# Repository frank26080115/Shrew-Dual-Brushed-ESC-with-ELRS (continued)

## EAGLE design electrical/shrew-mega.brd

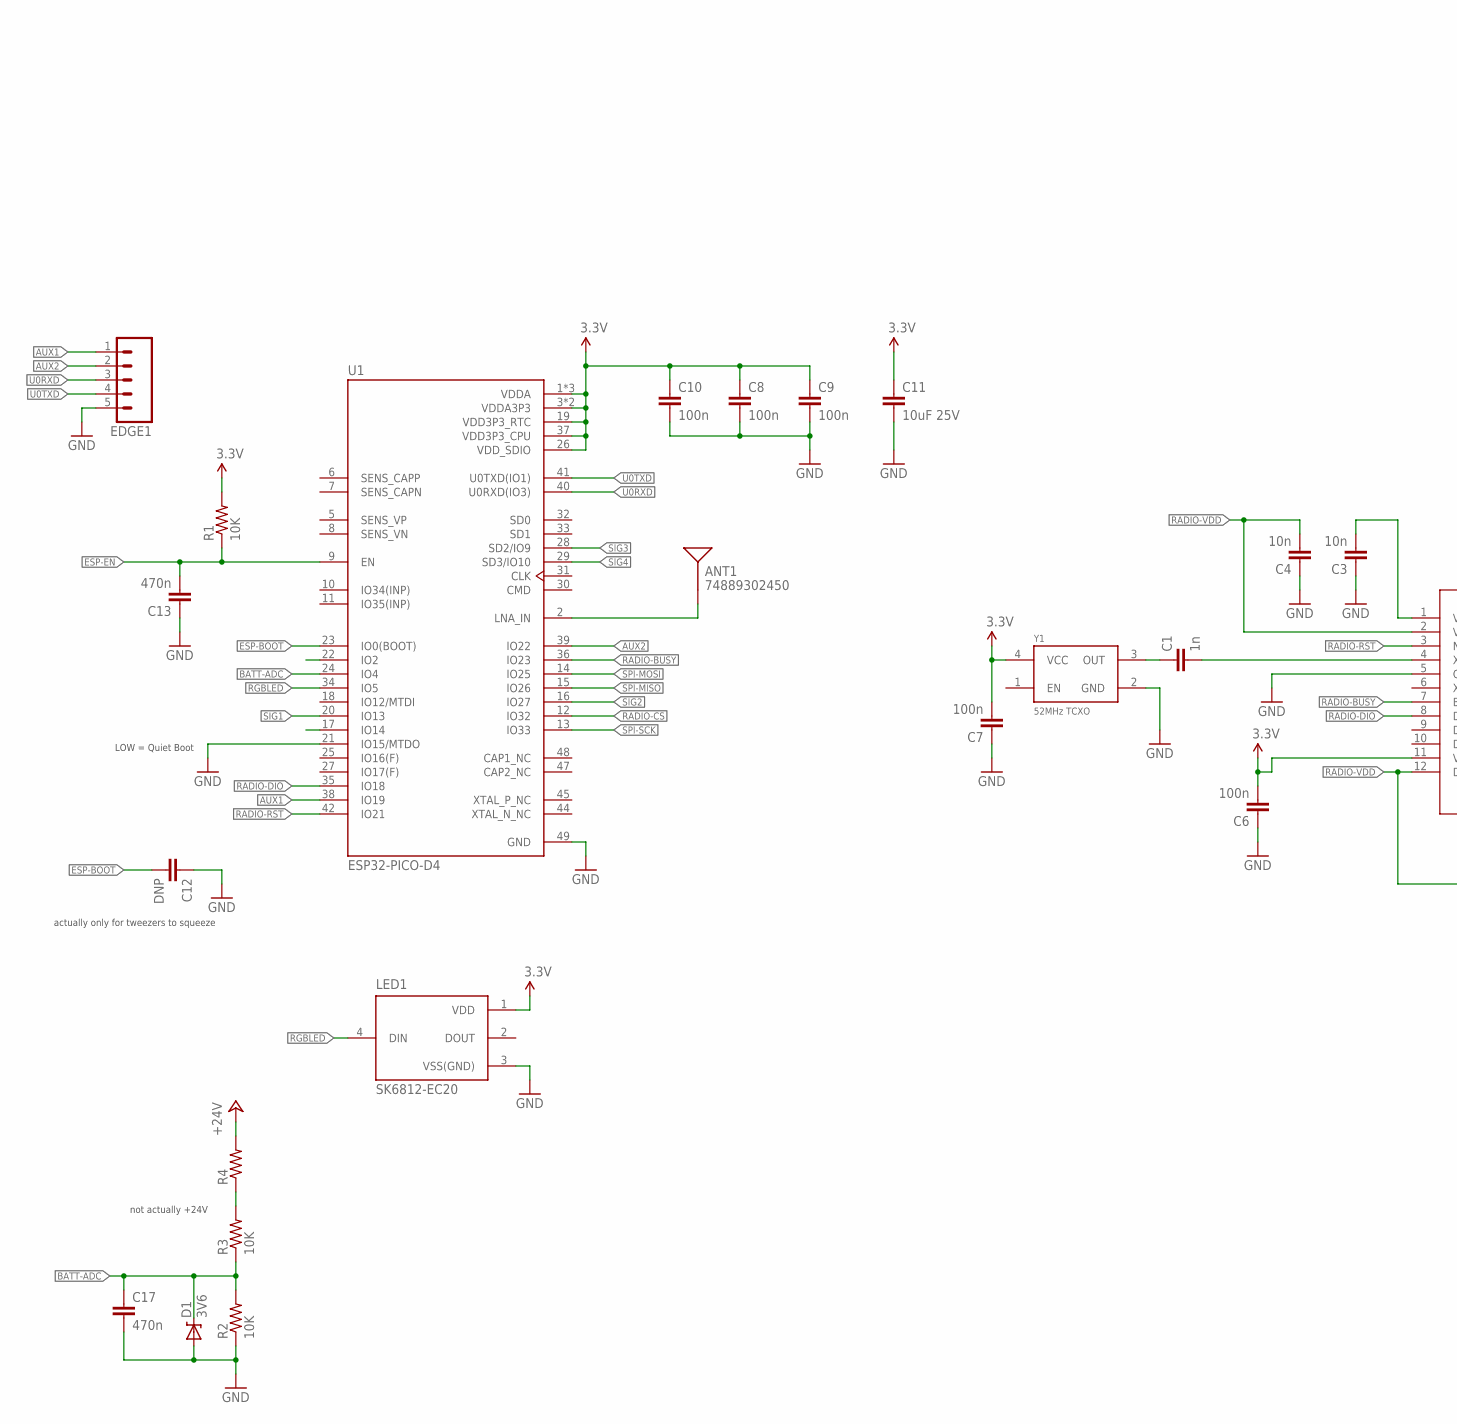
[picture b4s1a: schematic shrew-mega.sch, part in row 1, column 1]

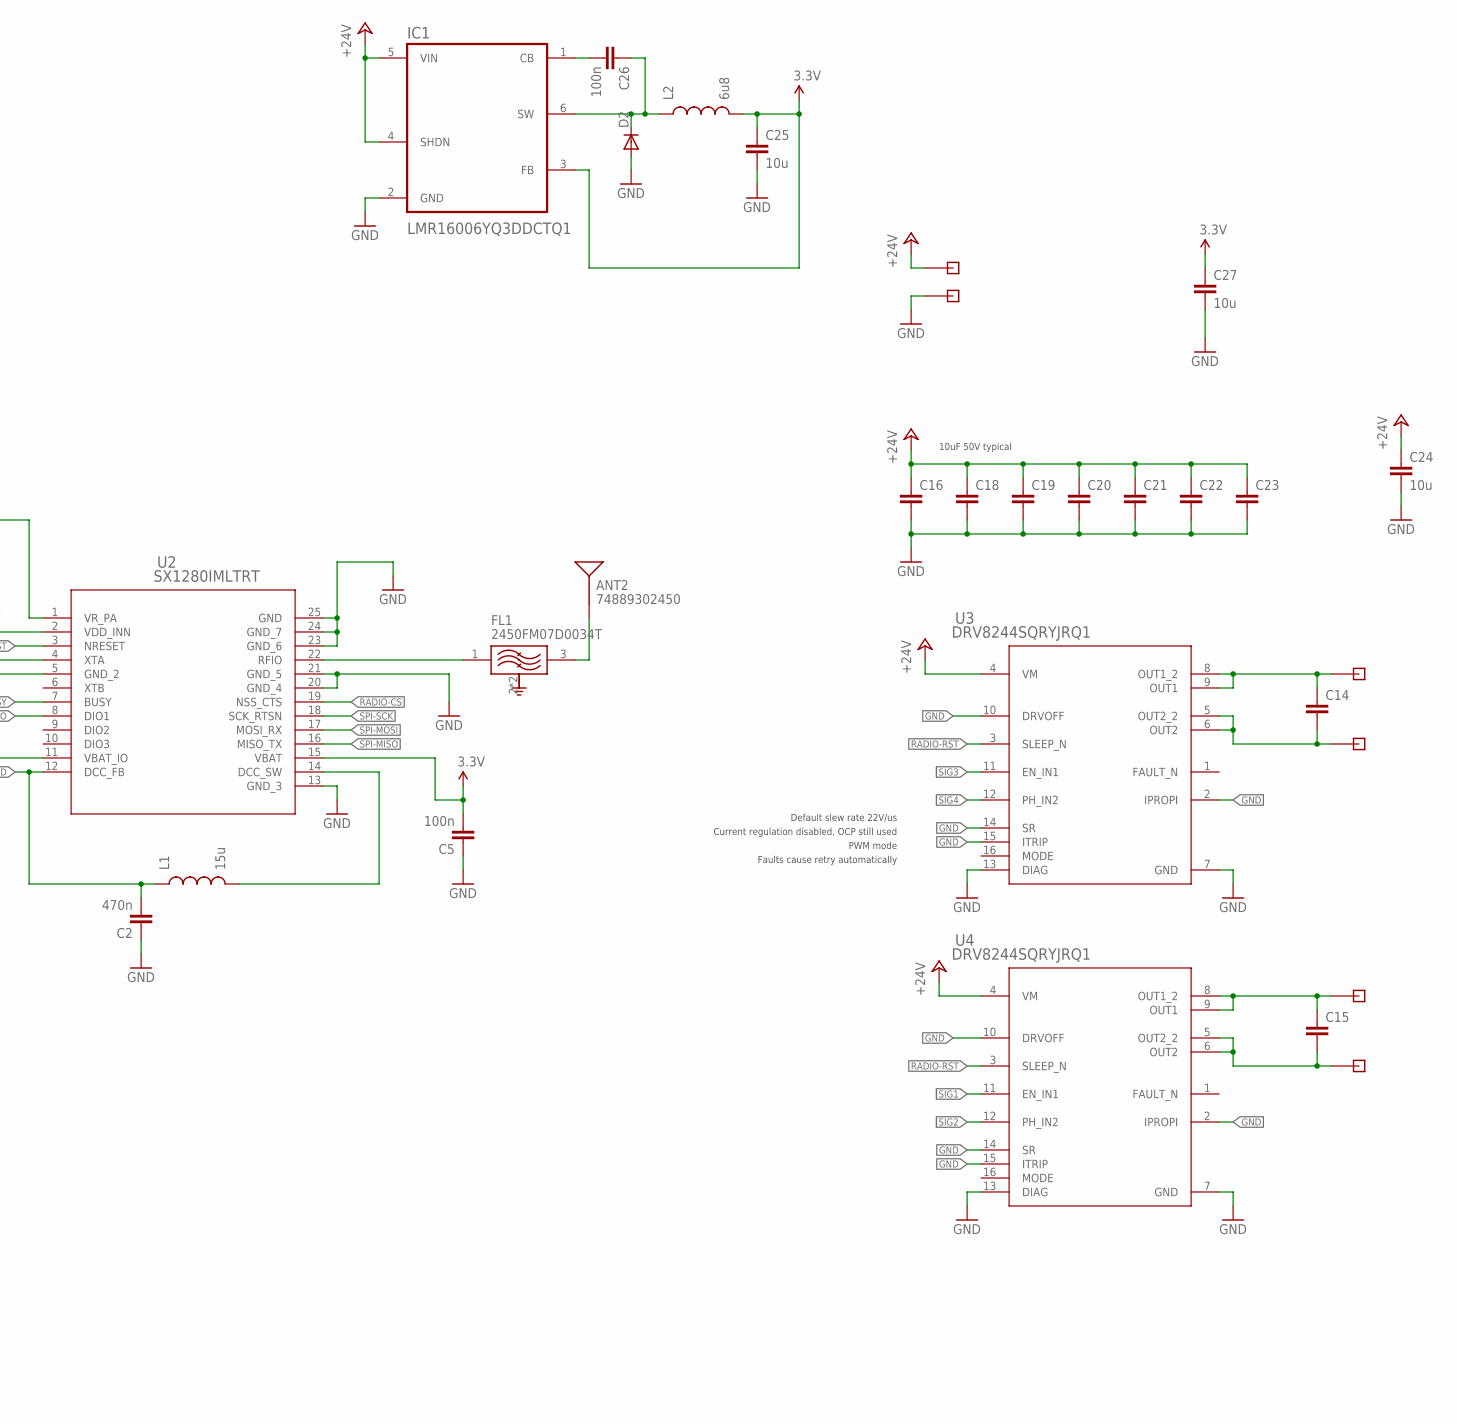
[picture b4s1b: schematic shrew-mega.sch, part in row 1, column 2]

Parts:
ANT1, ANT2: 74889302450; ANTENNA-CHIP2
C1: 1n; 0402-REV
C2, C13, C17: 470n; 0402-REV
C3, C4: 10n; 0402-REV
C5, C6, C7, C8, C9, C10, C26: 100n; 0402-REV
C11: 10uF 25V; 0805
C12: DNP; 0402-CAP
C14, C15: CAP0402-CAP; 0402-CAP
C16, C18, C19, C20, C21, C22, C23: CAP0805; 0805
C24, C25, C27: 10u; 0805
D1: 3V6; SOD-323
D2: DIODESOD; SOD-323
EDGE1: M05PTH; 1X05
FL1: 2450FM07D0034T; FIL_2450FM07D0034T
IC1: LMR16006YQ3DDCTQ1; SOT95P280X110-6N
L1: 15u; 0805
L2: 6u8; 0805
LED1: SK6812-EC20
R1, R2, R3: 10K; 0402-REV
R4: RESISTOR0402-REV; 0402-REV
U1: ESP32-PICO-D4; PQFN50P700X700X104-49N
U2: SX1280IMLTRT; QFN24_4X4_SEM
U3, U4: DRV8244SQRYJRQ1; RYJ0016A-MFG
X1, X2, X3, X4, X5, X6: PIN-1X-BIG; PAD-1X-BIG
Y1: 52MHz TCXO; OSC_TG2016SMN_50.0000M-ECGNNMB

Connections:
3.3V: C5.2, C6.2, C7.2, C8.1, C9.1, C10.1, C11.1, C25.1, C27.1, IC1.3 (FB), L2.2, LED1.1 (VDD), R1.2, U1.1 (VDDA), U1.3 (VDDA3P3), U1.4 (VDDA3P3), U1.19 (VDD3P3_RTC), U1.26 (VDD_SDIO), U1.37 (VDD3P3_CPU), U1.43 (VDDA), U1.46 (VDDA), U2.11 (VBAT_IO), U2.15 (VBAT), Y1.4 (VCC)
+24V: C16.1, C18.1, C19.1, C20.1, C21.1, C22.1, C23.1, C24.1, IC1.4 (SHDN), IC1.5 (VIN), R4.2, U3.4 (VM), U4.4 (VM), X5.1
AUX1: EDGE1.1, U1.38 (IO19)
AUX2: EDGE1.2, U1.39 (IO22)
BATT-ADC: C17.1, D1.1 (C), R2.2, R3.1, U1.24 (IO4)
ESP-BOOT: C12.2, U1.23 (IO0(BOOT))
ESP-EN: C13.2, R1.1, U1.9 (EN)
GND: C2.1, C3.1, C4.1, C5.1, C6.1, C7.1, C8.2, C9.2, C10.2, C11.2, C12.1, C13.1, C16.2, C17.2, C18.2, C19.2, C20.2, C21.2, C22.2, C23.2, C24.2, C25.2, C27.2, D1.2 (A), D2.2 (A), EDGE1.5, FL1.2 (GND), FL1.4 (GND), IC1.2 (GND), LED1.3 (VSS(GND)), R2.1, U1.21 (IO15/MTDO), U1.49 (GND), U2.5 (GND_2), U2.13 (GND_3), U2.20 (GND_4), U2.21 (GND_5), U2.23 (GND_6), U2.24 (GND_7), U2.25 (GND), U3.2 (IPROPI), U3.7 (GND), U3.10 (DRVOFF), U3.13 (DIAG), U3.14 (SR), U3.15 (ITRIP), U4.2 (IPROPI), U4.7 (GND), U4.10 (DRVOFF), U4.13 (DIAG), U4.14 (SR), U4.15 (ITRIP), X6.1, Y1.2 (GND)
MOTOR1: C14.1, U3.8 (OUT1_2), U3.9 (OUT1), X2.1
MOTOR2: C14.2, U3.5 (OUT2_2), U3.6 (OUT2), X1.1
MOTOR3: C15.1, U4.8 (OUT1_2), U4.9 (OUT1), X4.1
MOTOR4: C15.2, U4.5 (OUT2_2), U4.6 (OUT2), X3.1
unnamed: ANT1.FEED, U1.2 (LNA_IN)
unnamed: C1.1, Y1.3 (OUT)
unnamed: C1.2, U2.4 (XTA)
unnamed: C26.2, IC1.1 (CB)
unnamed: FL1.1 (IN), U2.22 (RFIO)
unnamed: ANT2.FEED, FL1.3 (OUT)
unnamed: L1.2, U2.14 (DCC_SW)
unnamed: C26.1, D2.1 (C), IC1.6 (SW), L2.1
unnamed: C3.2, U2.1 (VR_PA)
RADIO-BUSY: U1.36 (IO23), U2.7 (BUSY)
RADIO-CS: U1.12 (IO32), U2.19 (NSS_CTS)
RADIO-DIO: U1.35 (IO18), U2.8 (DIO1)
RADIO-RST: U1.42 (IO21), U2.3 (NRESET), U3.3 (SLEEP_N), U4.3 (SLEEP_N)
RADIO-VDD: C2.2, C4.2, L1.1, U2.2 (VDD_INN), U2.12 (DCC_FB)
RGBLED: LED1.4 (DIN), U1.34 (IO5)
SIG1: U1.20 (IO13), U4.11 (EN_IN1)
SIG2: U1.16 (IO27), U4.12 (PH_IN2)
SIG3: U1.28 (SD2/IO9), U3.11 (EN_IN1)
SIG4: U1.29 (SD3/IO10), U3.12 (PH_IN2)
SPI-MISO: U1.15 (IO26), U2.16 (MISO_TX)
SPI-MOSI: U1.14 (IO25), U2.17 (MOSI_RX)
SPI-SCK: U1.13 (IO33), U2.18 (SCK_RTSN)
U0RXD: EDGE1.3, U1.40 (U0RXD(IO3))
U0TXD: EDGE1.4, U1.41 (U0TXD(IO1))
V-ADC: R3.2, R4.1

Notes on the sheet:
actually only for tweezers to squeeze
not actually +24V
LOW = Quiet Boot
10uF 50V typical
Default slew rate 22V/us
Current regulation disabled, OCP still used
PWM mode
Faults cause retry automatically

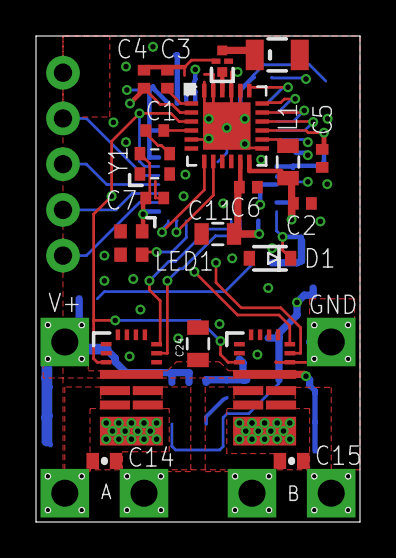
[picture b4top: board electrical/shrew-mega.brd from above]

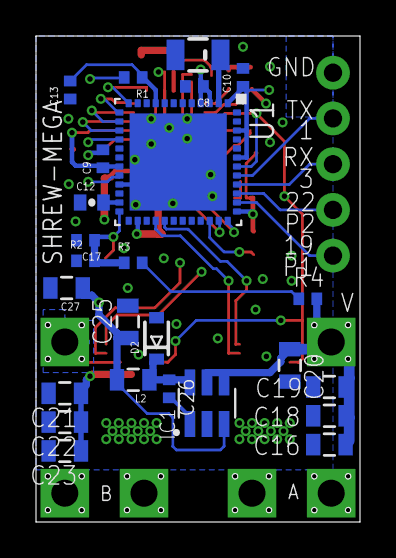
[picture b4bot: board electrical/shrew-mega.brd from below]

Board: 4 copper layers, 18.0 x 27.0 mm, 52 parts (25 on the bottom side), 37 nets.

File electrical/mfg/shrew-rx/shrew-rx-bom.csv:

Comment,Designator,Footprint,LCSC Part #
1n,C1,0402-CAP,
3V6,D1,SOD-323,
10K,R1 R2 R3,0402-RES,
10n,C3 C4,0402-CAP,
10uF 25V,C11,0805,
15u,L1,0805,
X1G0054410320,Y1,OSC_TG2016SMN_50.0000M-ECGNNMB,
100n,C5 C6 C7 C8 C9 C10,0402-CAP,
470n,C2 C13 C17,0402-CAP,
2450FM07D0034T,FL1,FIL_2450FM07D0034T,
74889302450,ANT1 ANT2,ANTENNA-CHIP2,
ESP32-PICO-D4,U1,PQFN50P700X700X104-49N,
SK6812-EC20,LED1,SK6812-EC20,
SX1280IMLTRT,U2,QFN24_4X4_SEM,

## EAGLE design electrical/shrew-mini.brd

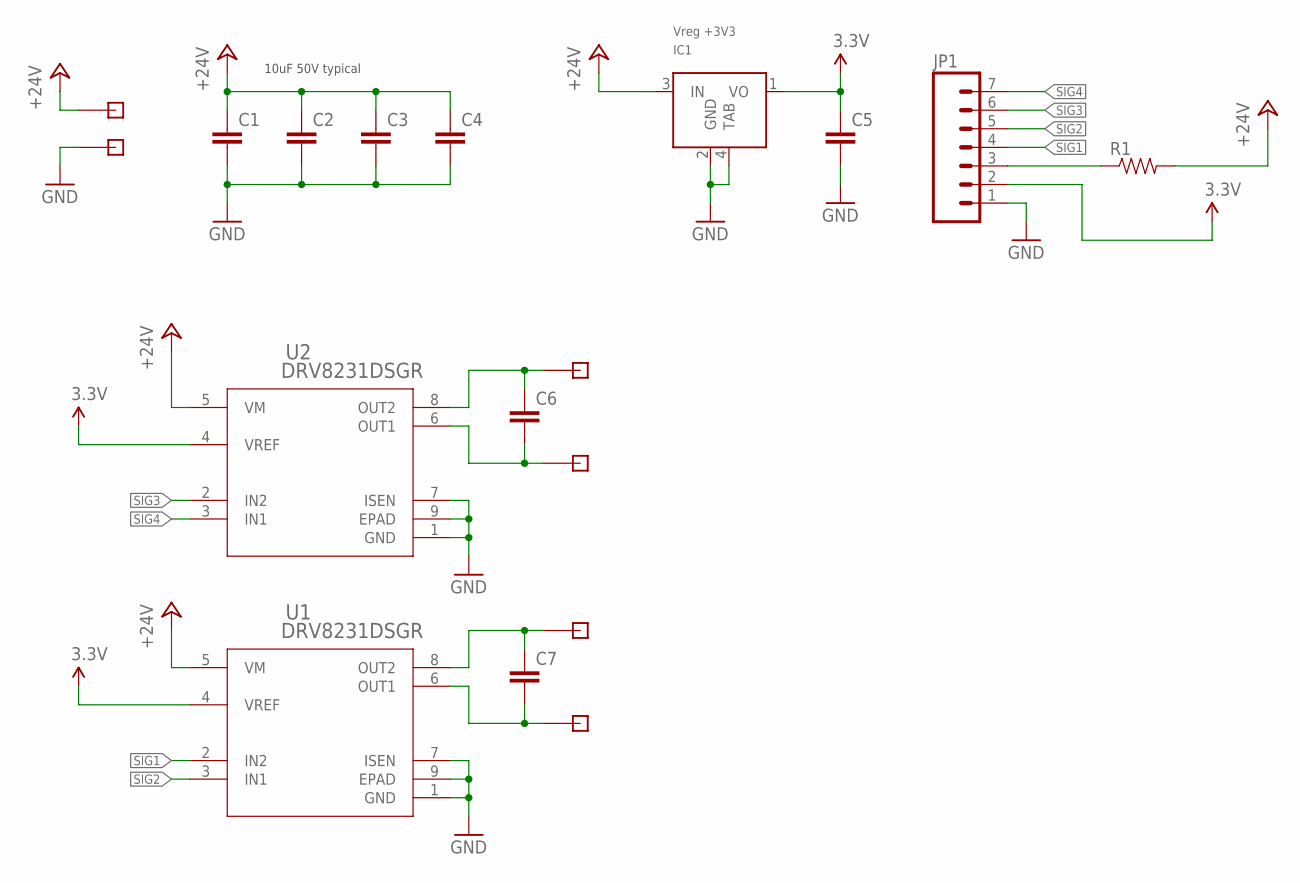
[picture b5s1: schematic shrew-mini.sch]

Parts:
C1, C2, C3, C4, C5: CAP0805; 0805
C6, C7: CAP0402-CAP; 0402-CAP
IC1: Vreg +3V3; SOT89
JP1: M07-2MM-TH; 1X07-2MM-TH
R1: RESISTOR0402-RES; 0402-RES
U1, U2: DRV8231DSGR; WSON8_DRV8231_TEX
X1, X2, X3, X4: PIN-1X-BIG; PAD-1X-BIG
X5, X6: PIN-1X-1.5MMSQ; PAD-1X-1.5MMSQ

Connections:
3.3V: C5.1, IC1.1 (VO), JP1.2, U1.4 (VREF), U2.4 (VREF)
+24V: C1.1, C2.1, C3.1, C4.1, IC1.3 (IN), R1.2, U1.5 (VM), U2.5 (VM), X5.P$1
GND: C1.2, C2.2, C3.2, C4.2, C5.2, IC1.2 (GND), IC1.4 (TAB), JP1.1, U1.1 (GND), U1.7 (ISEN), U1.9 (EPAD), U2.1 (GND), U2.7 (ISEN), U2.9 (EPAD), X6.P$1
MOTOR1: C7.2, U1.6 (OUT1), X3.1
MOTOR2: C7.1, U1.8 (OUT2), X4.1
MOTOR3: C6.2, U2.6 (OUT1), X1.1
MOTOR4: C6.1, U2.8 (OUT2), X2.1
SIG1: JP1.4, U1.2 (IN2)
SIG2: JP1.5, U1.3 (IN1)
SIG3: JP1.6, U2.2 (IN2)
SIG4: JP1.7, U2.3 (IN1)
V-ADC: JP1.3, R1.1

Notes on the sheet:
10uF 50V typical

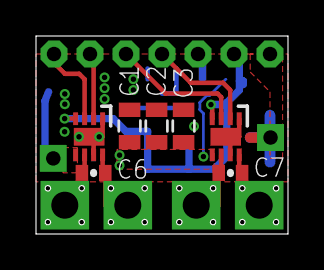
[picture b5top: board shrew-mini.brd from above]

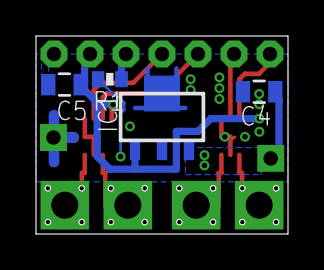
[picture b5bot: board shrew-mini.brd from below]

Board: 2 copper layers, 14.0 x 11.0 mm, 18 parts (4 on the bottom side), 12 nets.

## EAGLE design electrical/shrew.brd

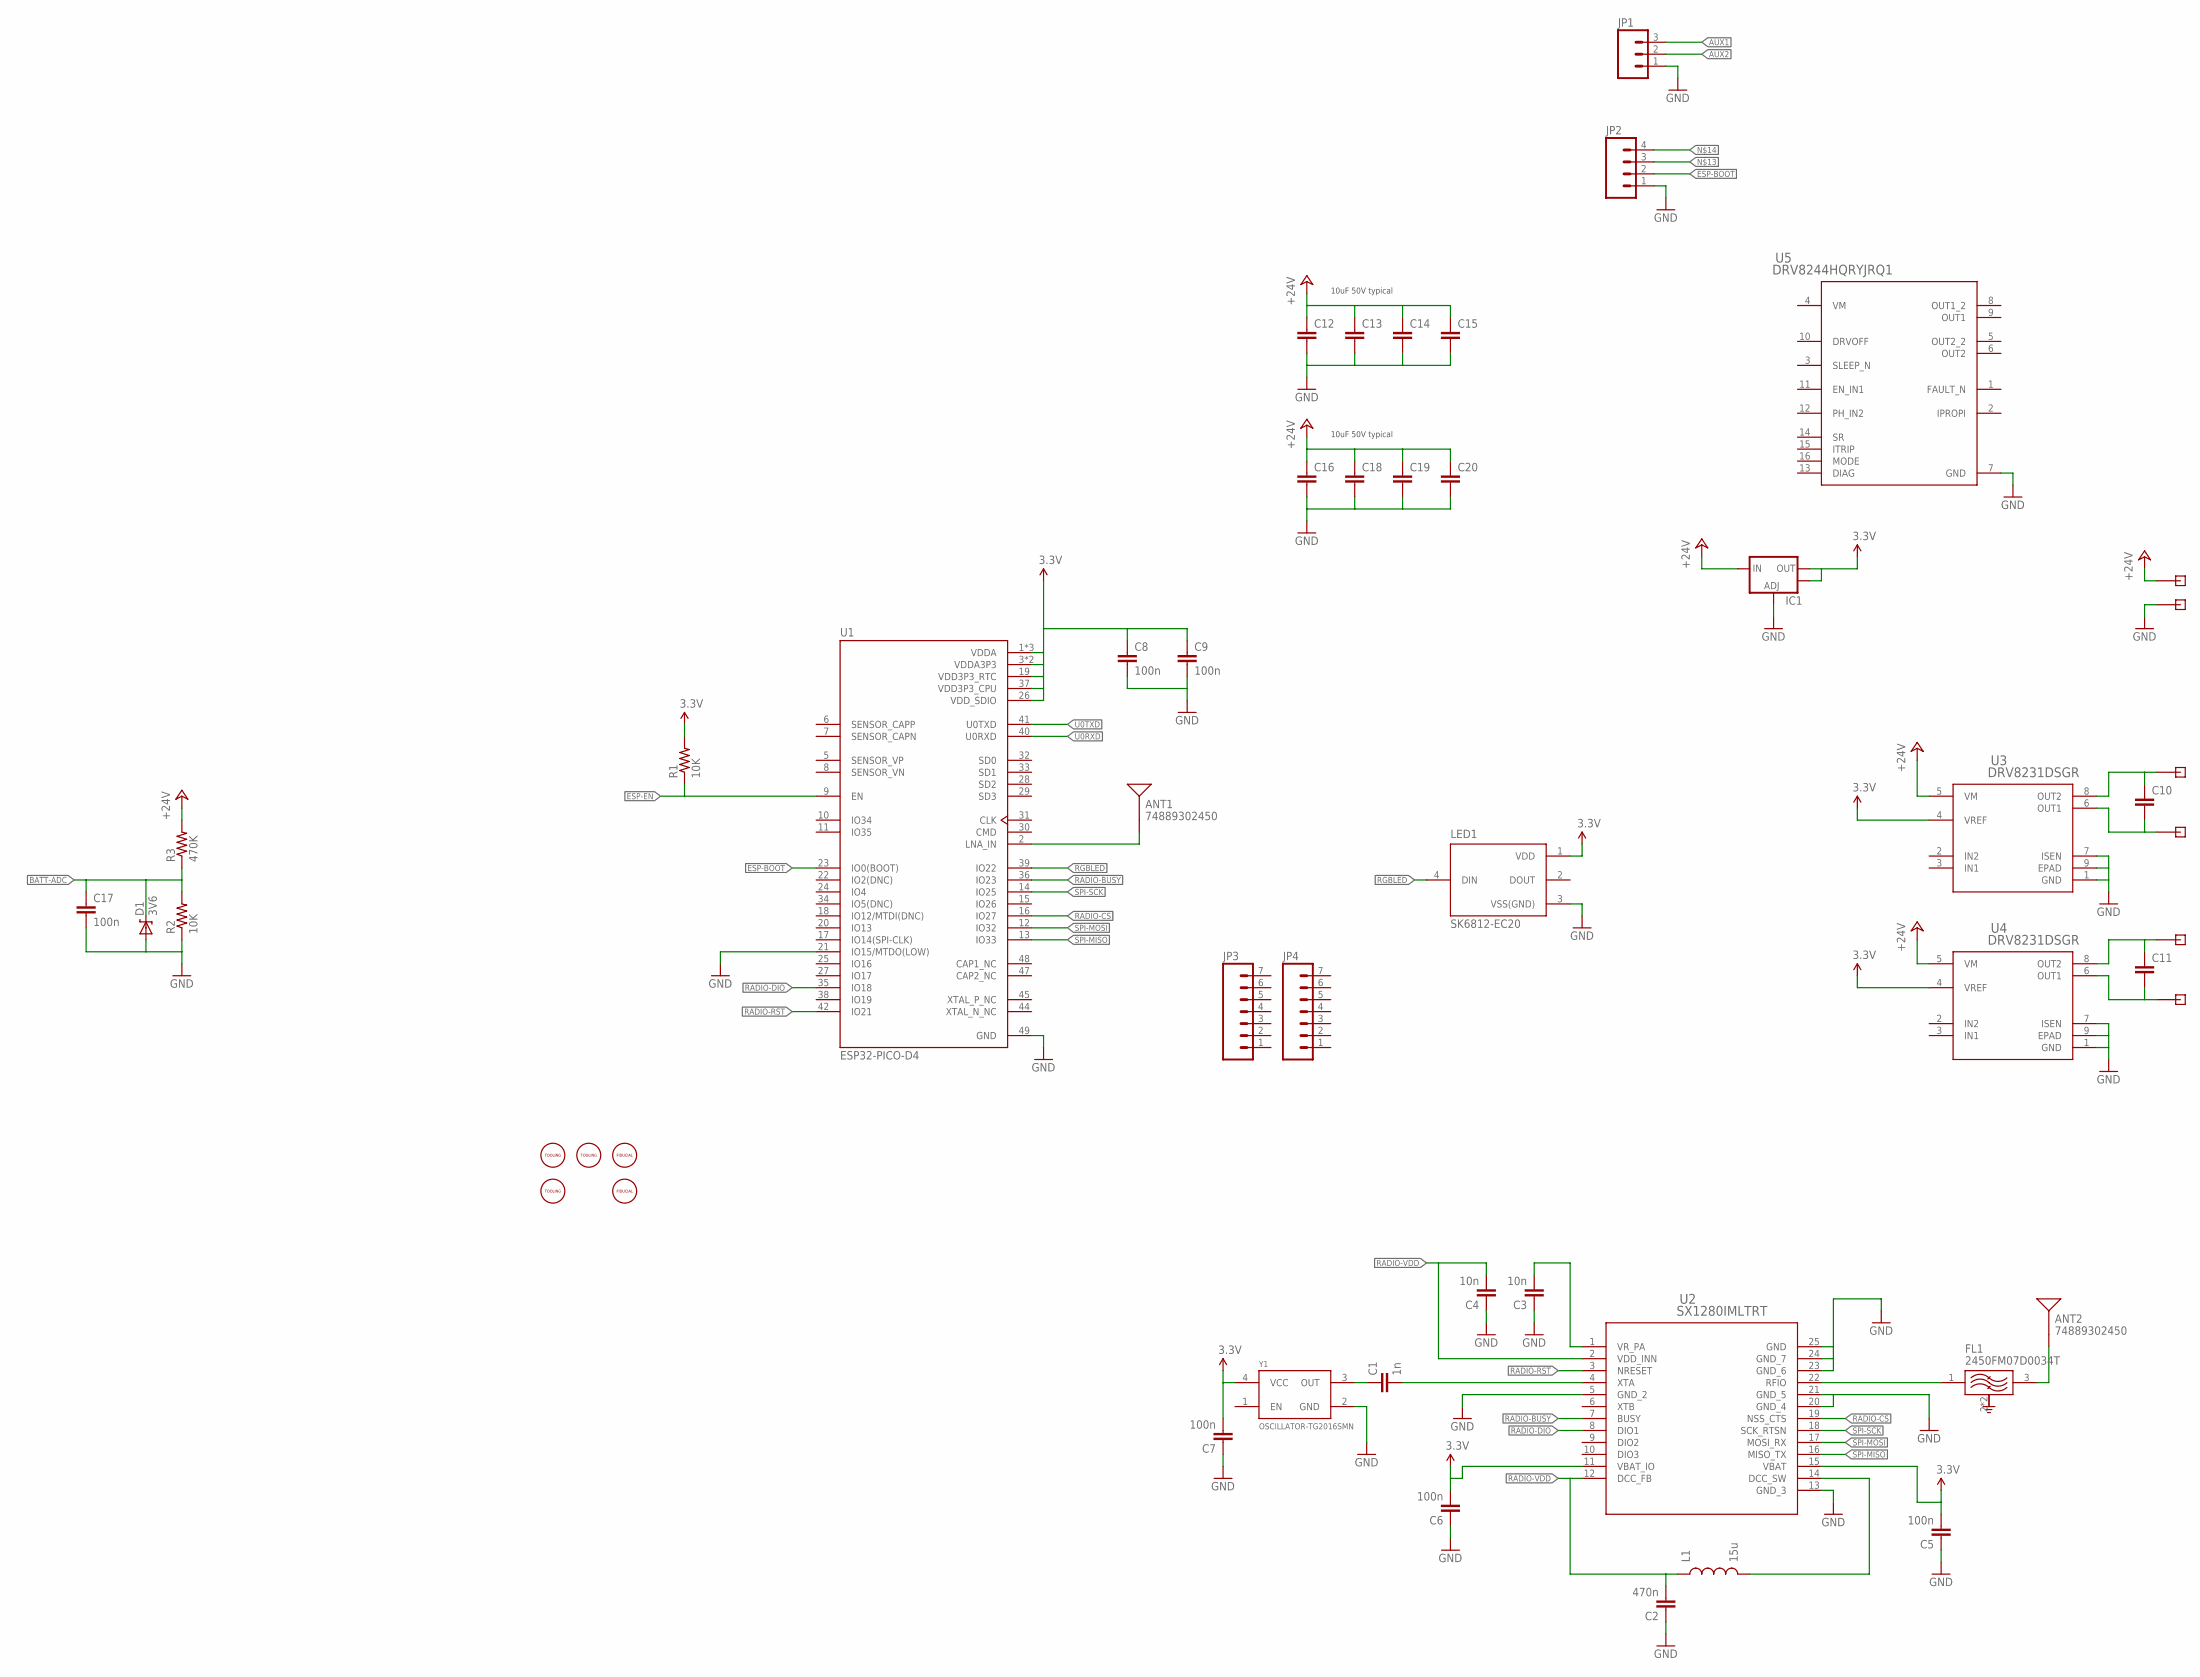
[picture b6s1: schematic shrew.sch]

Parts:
ANT1, ANT2: 74889302450; ANTENNA-CHIP2
C1: 1n; 0402-CAP
C2: 470n; 0402-CAP
C3, C4: 10n; 0402-CAP
C5, C6, C7, C8, C9, C17: 100n; 0402-CAP
C10, C11: CAP0402-CAP; 0402-CAP
C12, C13, C14, C15, C16, C18, C19, C20: CAP0805; 0805
D1: 3V6; SOD-323
FIDUCIAL1, FIDUCIAL2: FIDUCIAL-1MM-2MM
FL1: 2450FM07D0034T; FIL_2450FM07D0034T
IC1: V_REG_LM1117SOT223; SOT223
JP1: M03PTH; 1X03
JP2: M04PTH; 1X04
JP3, JP4: M07-2MM-TH; 1X07-2MM-TH
L1: 15u; 0805
LED1: SK6812-EC20
R1, R2: 10K; 0402-RES
R3: 470K; 0402-RES
TOOLING1, TOOLING2, TOOLING3: TOOLING-HOLE
U1: ESP32-PICO-D4; PQFN50P700X700X104-49N
U2: SX1280IMLTRT; QFN24_4X4_SEM
U3, U4: DRV8231DSGR; WSON8_DRV8231_TEX
U5: DRV8244HQRYJRQ1; RYJ0016A-MFG
X1, X2, X3, X4, X5, X6: PIN-1X-BIG; PAD-1X-BIG
Y1: OSCILLATOR-TG2016SMN; OSC_TG2016SMN_50.0000M-ECGNNMB

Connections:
3.3V: C5.2, C6.2, C7.2, C8.1, C9.1, IC1.2 (OUT), IC1.4 (OUT), LED1.1 (VDD), R1.2, U1.1 (VDDA), U1.3 (VDDA3P3), U1.4 (VDDA3P3), U1.19 (VDD3P3_RTC), U1.26 (VDD_SDIO), U1.37 (VDD3P3_CPU), U1.43 (VDDA), U1.46 (VDDA), U2.11 (VBAT_IO), U2.15 (VBAT), U3.4 (VREF), U4.4 (VREF), Y1.4 (VCC)
+24V: C12.1, C13.1, C14.1, C15.1, C16.1, C18.1, C19.1, C20.1, IC1.3 (IN), R3.2, U3.5 (VM), U4.5 (VM), X5.1
AUX1: JP1.3
AUX2: JP1.2
BATT-ADC: C17.1, D1.1 (C), R2.2, R3.1
ESP-BOOT: JP2.2, U1.23 (IO0(BOOT))
ESP-EN: R1.1, U1.9 (EN)
GND: C2.1, C3.1, C4.1, C5.1, C6.1, C7.1, C8.2, C9.2, C12.2, C13.2, C14.2, C15.2, C16.2, C17.2, C18.2, C19.2, C20.2, D1.2 (A), FL1.2 (GND), FL1.4 (GND), IC1.1 (ADJ), JP1.1, JP2.1, LED1.3 (VSS(GND)), R2.1, U1.21 (IO15/MTDO(LOW)), U1.49 (GND), U2.5 (GND_2), U2.13 (GND_3), U2.20 (GND_4), U2.21 (GND_5), U2.23 (GND_6), U2.24 (GND_7), U2.25 (GND), U3.1 (GND), U3.7 (ISEN), U3.9 (EPAD), U4.1 (GND), U4.7 (ISEN), U4.9 (EPAD), U5.7 (GND), X6.1, Y1.2 (GND)
unnamed: ANT1.FEED, U1.2 (LNA_IN)
unnamed: C1.1, Y1.3 (OUT)
unnamed: C1.2, U2.4 (XTA)
unnamed: C10.2, U3.6 (OUT1), X1.1
unnamed: C10.1, U3.8 (OUT2), X2.1
unnamed: FL1.1 (IN), U2.22 (RFIO)
unnamed: ANT2.FEED, FL1.3 (OUT)
unnamed: C11.2, U4.6 (OUT1), X3.1
unnamed: L1.2, U2.14 (DCC_SW)
unnamed: C11.1, U4.8 (OUT2), X4.1
unnamed: C3.2, U2.1 (VR_PA)
RADIO-BUSY: U1.36 (IO23), U2.7 (BUSY)
RADIO-CS: U1.16 (IO27), U2.19 (NSS_CTS)
RADIO-DIO: U1.35 (IO18), U2.8 (DIO1)
RADIO-RST: U1.42 (IO21), U2.3 (NRESET)
RADIO-VDD: C2.2, C4.2, L1.1, U2.2 (VDD_INN), U2.12 (DCC_FB)
RGBLED: LED1.4 (DIN), U1.39 (IO22)
SPI-MISO: U1.13 (IO33), U2.16 (MISO_TX)
SPI-MOSI: U1.12 (IO32), U2.17 (MOSI_RX)
SPI-SCK: U1.14 (IO25), U2.18 (SCK_RTSN)
U0RXD: U1.40 (U0RXD)
U0TXD: U1.41 (U0TXD)

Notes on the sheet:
10uF 50V typical

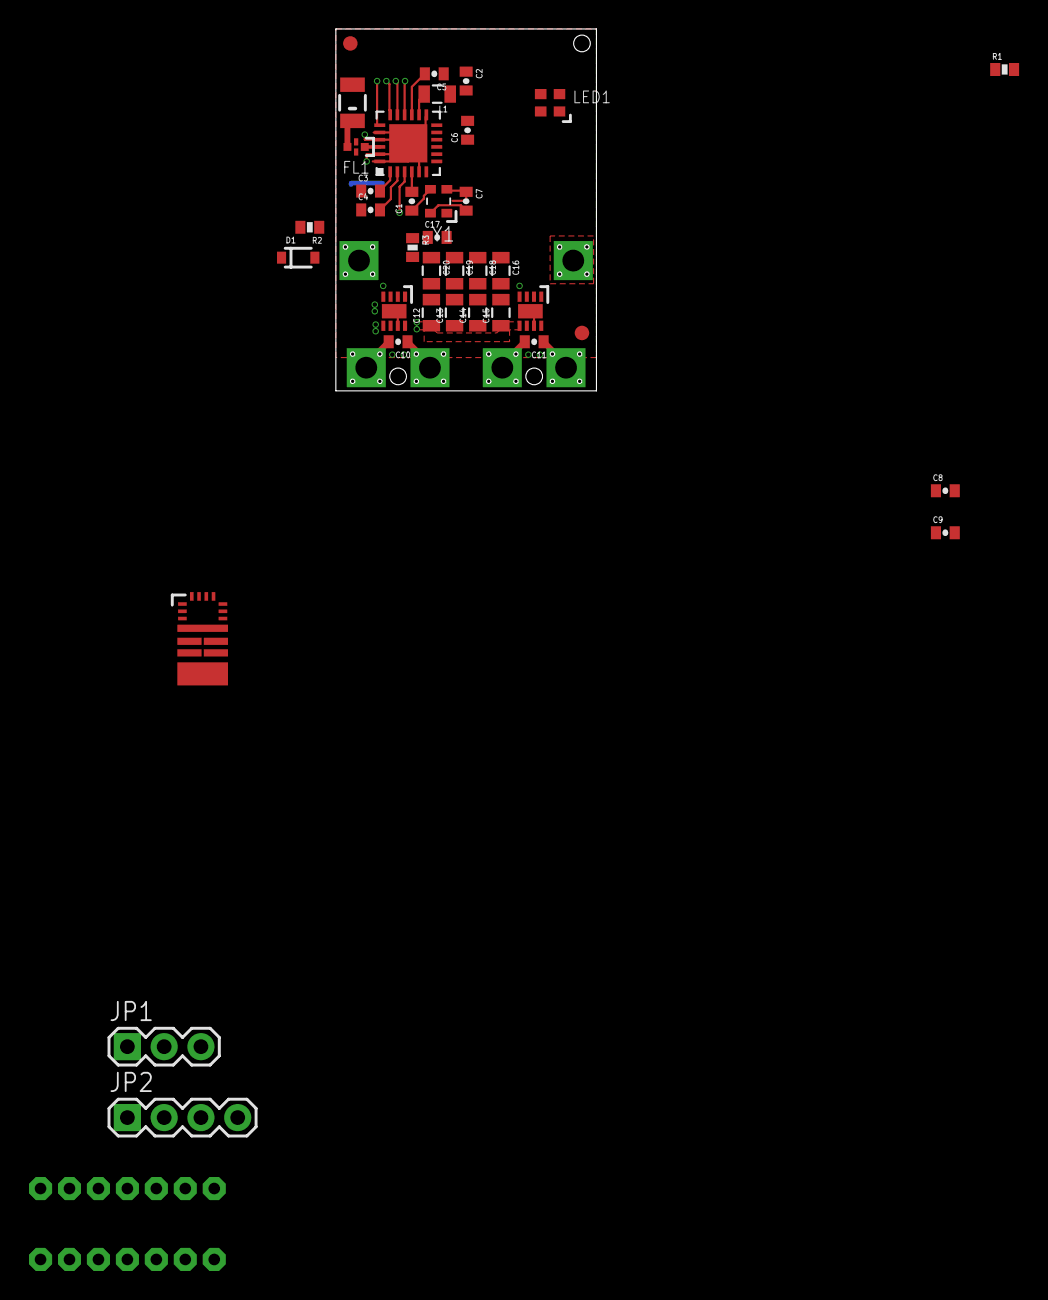
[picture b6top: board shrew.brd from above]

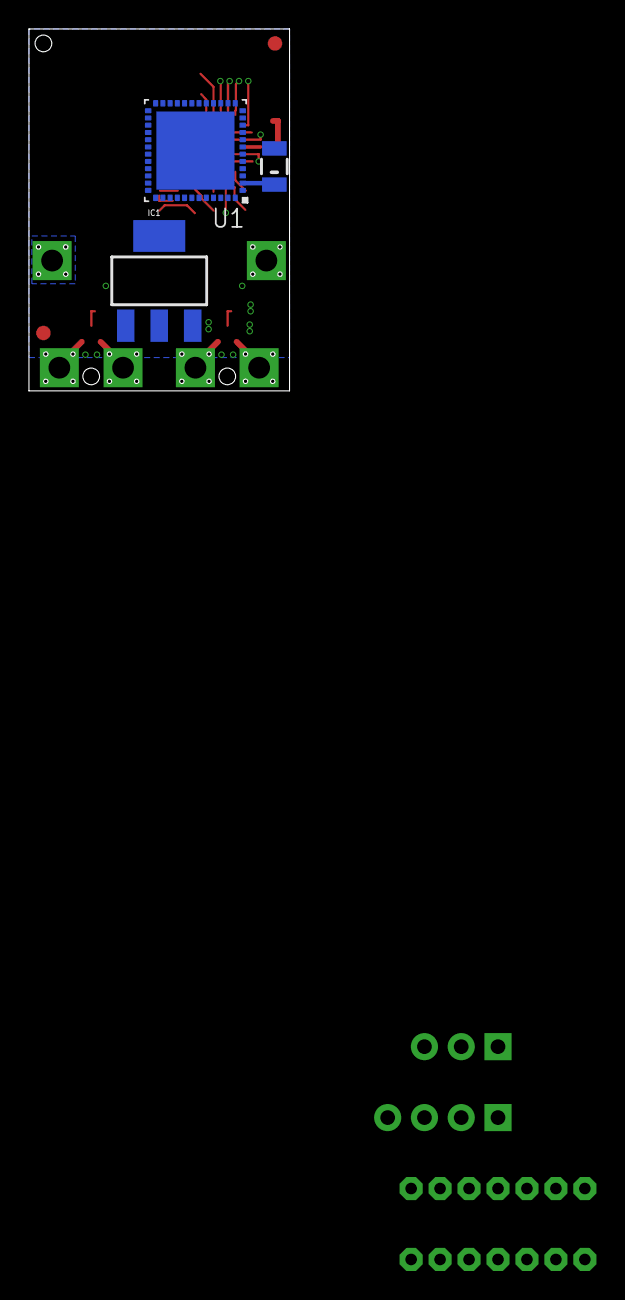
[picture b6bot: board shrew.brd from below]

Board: 2 copper layers, 18.0 x 25.0 mm, 51 parts (3 on the bottom side), 26 nets.

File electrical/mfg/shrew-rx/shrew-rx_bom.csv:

Comment,Designator,Footprint,LCSC Part #
1n,C1,0402-CAP,
3V6,D1,SOD-323,
10K,R1 R2 R3,0402-RES,
10n,C3 C4,0402-CAP,
10uF 25V,C11,0805,
15u,L1,0805,
52MHz TCXO,Y1,OSC_TG2016SMN_50.0000M-ECGNNMB,
100n,C5 C6 C7 C8 C9 C10,0402-CAP,
470n,C2 C13 C17,0402-CAP,
2450FM07D0034T,FL1,FIL_2450FM07D0034T,
74889302450,ANT1 ANT2,ANTENNA-CHIP2,
ESP32-PICO-D4,U1,PQFN50P700X700X104-49N,
SK6812-EC20,LED1,SK6812-EC20,
SX1280IMLTRT,U2,QFN24_4X4_SEM,

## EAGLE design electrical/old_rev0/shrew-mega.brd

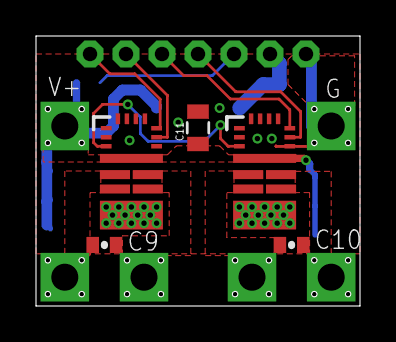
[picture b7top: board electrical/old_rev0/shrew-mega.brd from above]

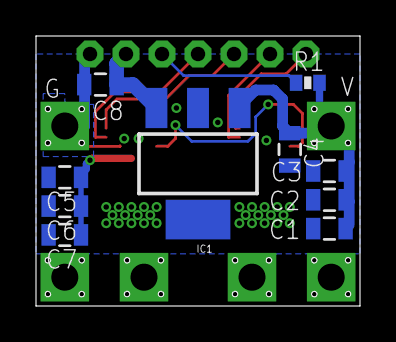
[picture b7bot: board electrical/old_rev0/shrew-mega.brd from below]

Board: 2 copper layers, 18.0 x 15.0 mm, 22 parts (10 on the bottom side), 13 nets.

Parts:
C1, C2, C3, C4, C5, C6, C7, C8, C11: 0805
C9, C10: 0402-CAP
IC1: SOT223
JP1: 1X07-2MM-TH
R1: 0402-RES
U1, U2: DRV8244SQRYJRQ1; RYJ0016A-MFG
X1, X2, X3, X4, X5, X6: PIN-1X-BIG; PAD-1X-BIG

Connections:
3.3V: C8.1, IC1.3, JP1.2
+24V: C1.1, C2.1, C3.1, C4.1, C5.1, C6.1, C7.1, C11.1, IC1.1, R1.2, U1.4, U2.4, X5.1
GND: C1.2, C2.2, C3.2, C4.2, C5.2, C6.2, C7.2, C8.2, C11.2, IC1.2, IC1.4, JP1.1, U1.2, U1.7, U1.10, U1.13, U1.14, U1.15, U2.2, U2.7, U2.10, U2.13, U2.14, U2.15, X6.1
MOTOR1: C9.1, U1.8, U1.9, X2.1
MOTOR2: C9.2, U1.5, U1.6, X1.1
MOTOR3: C10.1, U2.8, U2.9, X4.1
MOTOR4: C10.2, U2.5, U2.6, X3.1
SIG1: JP1.4, U2.11
SIG2: JP1.5, U2.12
SIG3: JP1.6, U1.11
SIG4: JP1.7, U1.12
SLEEP: U1.3, U2.3
V-ADC: JP1.3, R1.1

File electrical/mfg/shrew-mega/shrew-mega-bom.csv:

Comment,Designator,Footprint,
100nF 50V,C9,0402-CAP,
100nF 50V,C10,0402-CAP,
62K,R1,0402-RES,
10uF 50V,C1,0805,
10uF 50V,C2,0805,
10uF 50V,C3,0805,
10uF 50V,C4,0805,
10uF 50V,C5,0805,
10uF 50V,C6,0805,
10uF 50V,C7,0805,
10uF 50V,C8,0805,
MIC5239-3.3YS-TR,IC1,SOT223,
DRV8244HQRYJRQ1,U1 U2,QFN,

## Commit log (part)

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2024-06-07 starting to gather parts for the pcb parts library
2024-06-09 wip, before splitting board into modules
2024-06-09 wip, rx modularized
2024-06-09 wip for rx
2024-06-09 datasheets
2024-06-09 mini board
2024-06-10 rx mfg file trial run
2024-06-10 more mfg files
2024-06-10 file name changes so JLCPCB autodetects
2024-06-12 changed v-reg on the mega variant to be more avail
2024-06-12 doc update
2024-06-13 gerbv project files
2024-06-13 mfg file improvements, fixed drill file error
2024-06-27 RX BOM and CPL update
2024-06-29 schematic stitcher
2024-06-30 added better 0402 footprint to lib
2024-06-30 changed all 0402 footprints on rx
2024-07-02 added power input silk
2024-07-02 add net renaming to stitcher
2024-07-12 fw_bringup sketches
2024-07-13 update revision zero doc with thermal tests
2024-07-14 update doc for revision zero
2024-07-15 revision zero added xtal freq test
2024-07-15 added photo of revision 0
2024-07-17 new shrew rev0 photo
2024-07-18 rev 0 doc, mega continuous current test
2024-07-18 rev 0 doc updated with mini continuous test
2024-08-08 initial work on integrated versions
2024-08-08 up-rev
2024-08-08 rev0
2024-08-08 moved the stitching script
2024-08-08 second gen gerbers
2024-08-09 placed a PCBA order for shrew-lite
2024-08-10 ordered programmer PCB
2024-08-11 added shrew-zero, fixed some inner planes to avoid antenna
2024-08-11 shrew-zero bom
2024-08-12 shrew-zero major update
2024-08-12 rotation of clock
2024-08-15 sorted component ref des
2024-08-27 shrew zero user manual and firmware
2024-08-27 update shrew zero doc with dimensions, no 3cyc bind
2024-08-28 user manual changes, and added mixes
2024-08-28 added image of USB adapter cable
2024-08-28 missed the url in some docs
2024-08-28 shrew pro prototype sent off to manufacturing
2024-08-28 cosmetic tweaks to zero pcb
2024-08-28 added led blink animations
2024-08-28 update led blink tables
2024-08-29 updated wifi LED animation documentation
2024-08-29 firmware files for delivery
2024-08-30 shrew-lite new buck vreg
2024-08-30 shrew-lite buck vreg wip, shorter
2024-08-30 shrew-lite another prototype order
2024-09-01 shrew zero layout improvements
2024-09-03 shrew zero next prototype ready to mfg
2024-09-05 shrew zero another mfg run
2024-09-05 another programmer PCB
2024-09-12 update front page to reflect newest designs
2024-09-19 added smoke stopper document
2024-09-20 documentation update
2024-09-20 shrew-pro pin silk screen label fix
2024-09-20 shrew lite update pin labelling
2024-10-02 shrew dev kit for annihilation robotics
2024-10-02 added developer's build guide
2024-10-03 easily accessible schematic images
2024-10-05 user manual updates
2024-10-09 add doc explaining motor driver specs
2024-10-16 starting the fcc test gui for sx1280
2024-10-16 work on fcc test bench gui
2024-10-21 shrew-pro with additional capacitors
2024-10-21 fcc test bench bare minimum functionality
2024-10-21 added document for reassigning pins
2024-10-21 added chinese to fcc test bench
2024-10-22 fcc test bench working
2024-10-22 missed one junction (graphical change only)
2024-10-23 new fcc test requirements
2024-10-25 test bench working freq hop
2024-10-28 fcc story first upload, wip
2024-10-28 fcc story wip
2024-11-01 PCB changes for better EMI emissions
2024-11-02 shrew zero added reverse protection diode
2024-11-02 update smoke stopper page with link to RR
2024-11-05 minor edits during PCB ordering
2024-11-23 upload a bunch of EDN articles for FCC
2024-11-23 new firmware bins
2025-01-01 uploading user manuals to new directory
2025-01-01 moved user manuals, adding redirects
2025-01-01 added new dev firmware build
2025-01-01 added blinky firmware
2025-02-07 xr2 mod start
2025-02-09 updated pin map for xr2
2025-02-25 xr2 mod update with firmware file
2025-03-26 del old fw bins
2025-05-26 add AM32 fw with more robust dshot
2025-05-26 dshot1200 builds off of dev
2025-12-13 mixer test builds 20251212
